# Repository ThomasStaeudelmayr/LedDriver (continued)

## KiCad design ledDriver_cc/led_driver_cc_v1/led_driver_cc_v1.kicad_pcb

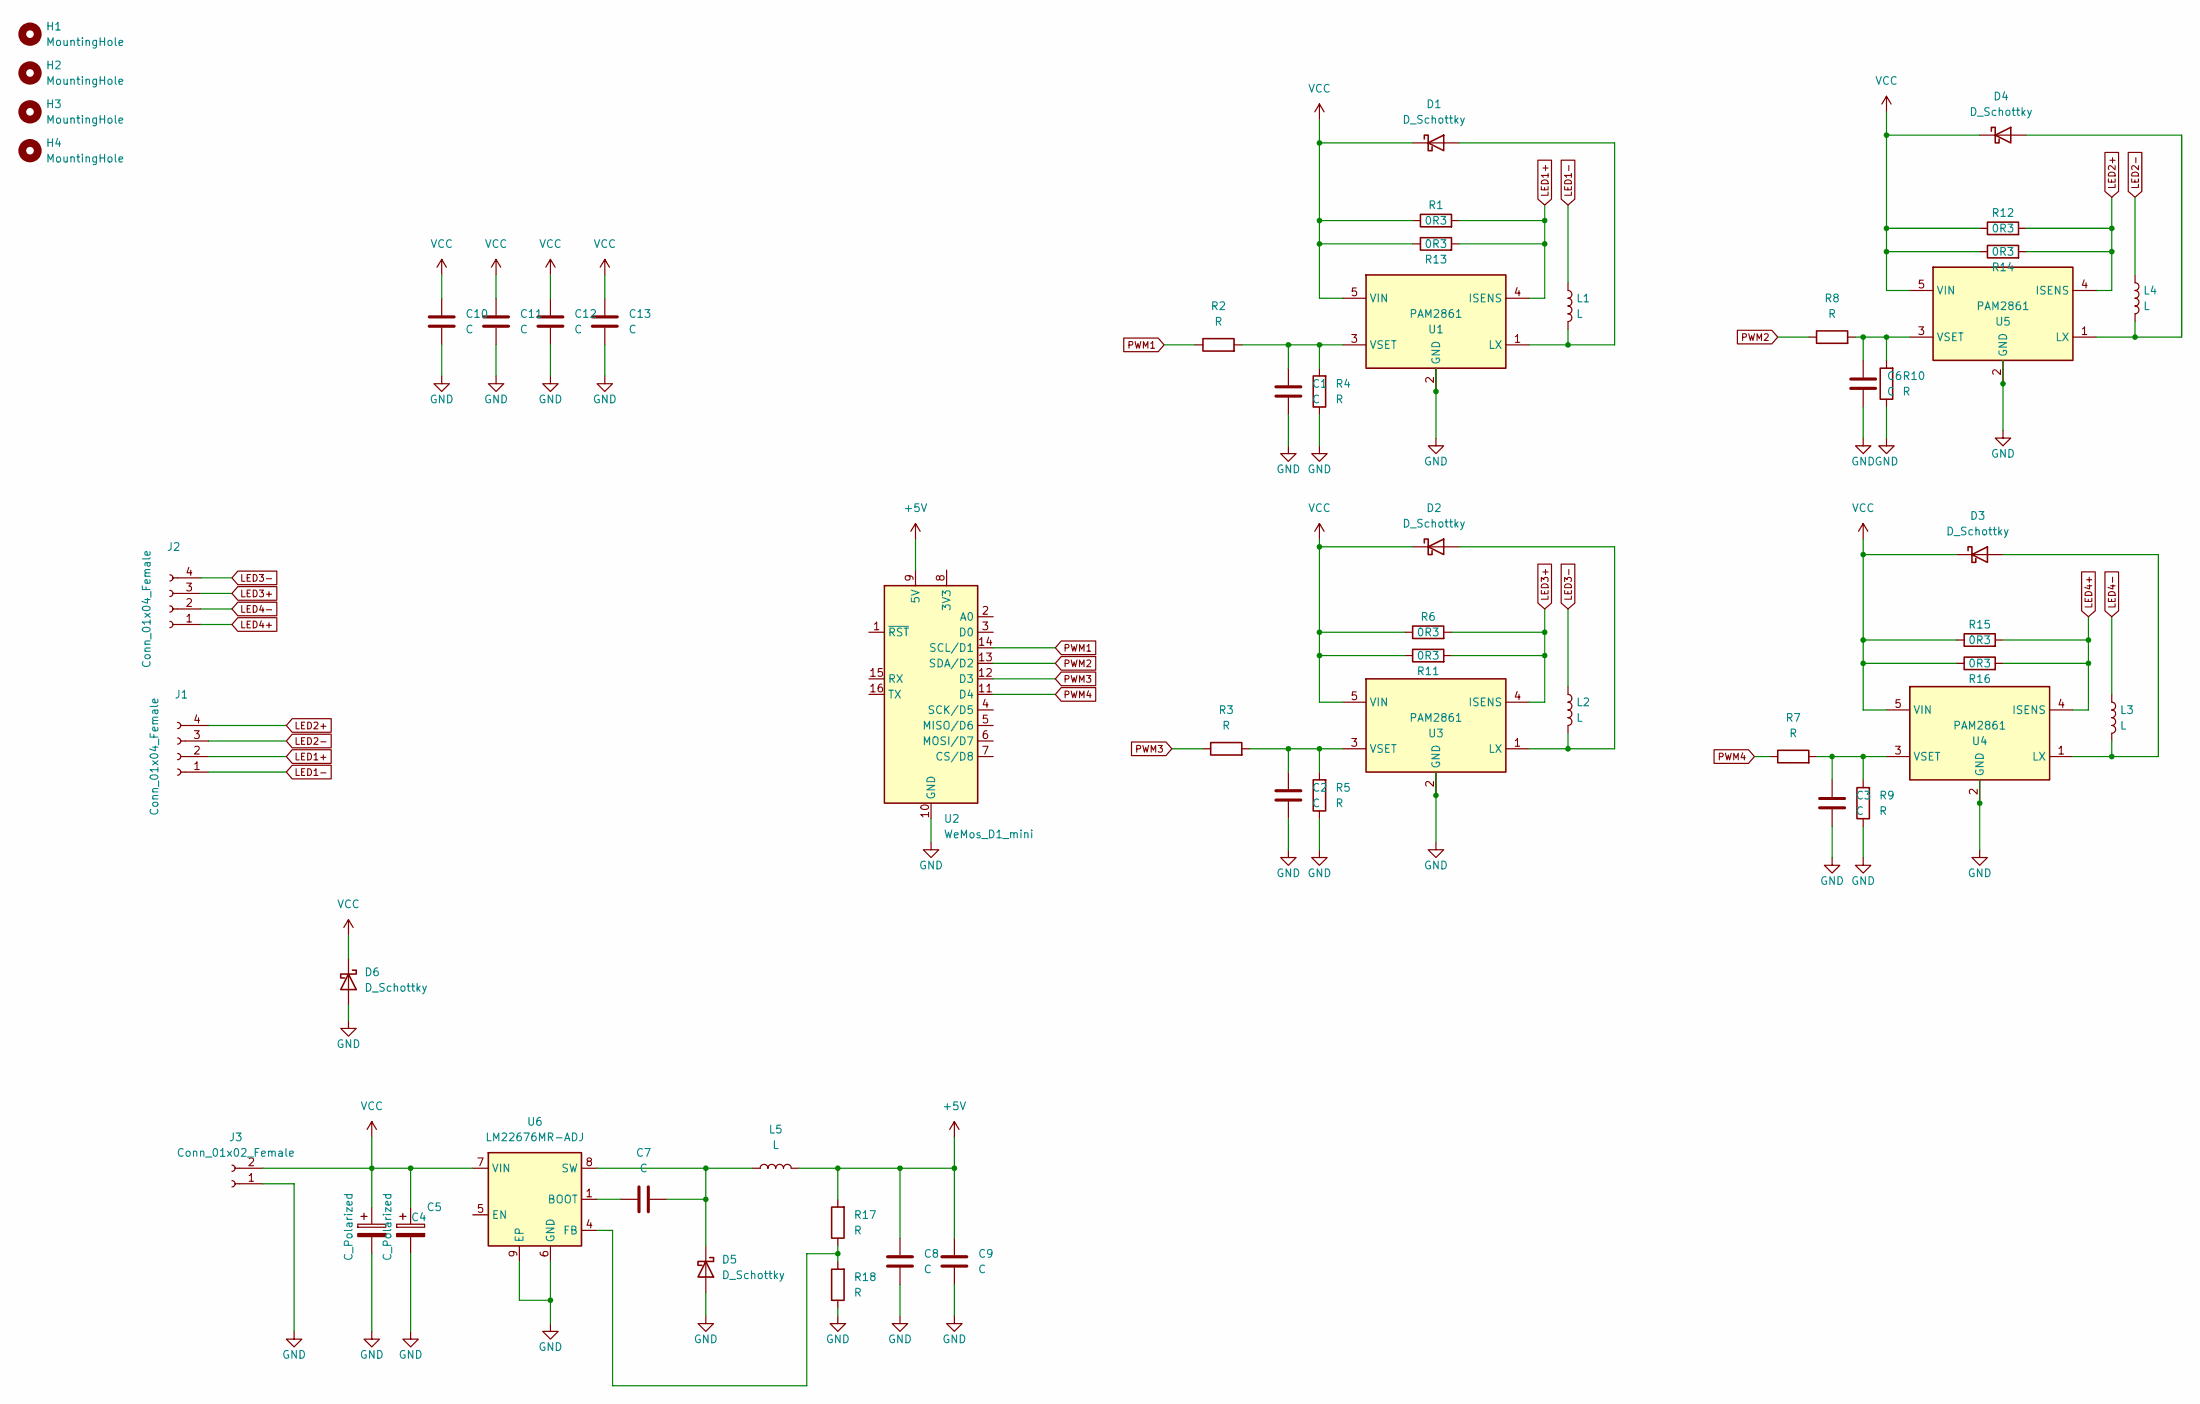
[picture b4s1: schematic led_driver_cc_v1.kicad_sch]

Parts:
C1, C2, C3, C6, C7: C; C_1206_3216Metric_Pad1.33x1.80mm_HandSolder
C4, C5: C_Polarized; CP_Radial_D13.0mm_P5.00mm
C8, C9, C10, C11, C12, C13: C; C_1210_3225Metric_Pad1.33x2.70mm_HandSolder
D1, D2, D3, D4, D5: D_Schottky; D_SMB
D6: D_Schottky; D_SMC
H1, H2, H3, H4: MountingHole; MountingHole_2.7mm_M2.5_DIN965_Pad_TopBottom
J1, J2: Conn_01x04_Female; PhoenixContact_MSTBVA_2,5_4-G_1x04_P5.00mm_Vertical
J3: Conn_01x02_Female; PhoenixContact_MSTBVA_2,5_2-G_1x02_P5.00mm_Vertical
L1, L2, L3, L4, L5: L; L_10.4x10.4_H4.8
R1, R6, R11, R12, R13, R14, R15, R16: 0R3; R_1206_3216Metric
R2, R3, R4, R5, R7, R8, R9, R10, R17, R18: R; R_1206_3216Metric
U1, U3, U4, U5: PAM2861; SOT-89
U2: WeMos_D1_mini; WEMOS_D1_mini_light
U6: LM22676MR-ADJ; TI_SO-PowerPAD-8

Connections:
+5V: C8.1, C9.1, L5.2, R17.2, U2.9 (5V)
GND: C1.2, C2.2, C3.2, C4.2, C5.2, C6.2, C8.2, C9.2, C10.2, C11.2, C12.2, C13.2, D5.2 (A), D6.2 (A), J3.1, R4.1, R5.1, R9.1, R10.1, R18.1, U1.2 (GND), U2.10 (GND), U3.2 (GND), U4.2 (GND), U5.2 (GND), U6.6 (GND), U6.9 (EP)
LED1+: J1.2, R1.2, R13.2, U1.4 (ISENS)
LED1-: J1.1, L1.1
LED2+: J1.4, R12.2, R14.2, U5.4 (ISENS)
LED2-: J1.3, L4.1
LED3+: J2.3, R6.2, R11.2, U3.4 (ISENS)
LED3-: J2.4, L2.1
LED4+: J2.1, R15.2, R16.2, U4.4 (ISENS)
LED4-: J2.2, L3.1
unnamed: C1.1, R2.2, R4.2, U1.3 (VSET)
unnamed: C2.1, R3.2, R5.2, U3.3 (VSET)
unnamed: C3.1, R7.2, R9.2, U4.3 (VSET)
unnamed: C6.1, R8.2, R10.2, U5.3 (VSET)
unnamed: C7.1, U6.1 (BOOT)
unnamed: C7.2, D5.1 (K), L5.1, U6.8 (SW)
unnamed: D1.2 (A), L1.2, U1.1 (LX)
unnamed: D2.2 (A), L2.2, U3.1 (LX)
unnamed: D3.2 (A), L3.2, U4.1 (LX)
unnamed: D4.2 (A), L4.2, U5.1 (LX)
unnamed: R17.1, R18.2, U6.4 (FB)
PWM1: R2.1, U2.14 (SCL/D1)
PWM2: R8.1, U2.13 (SDA/D2)
PWM3: R3.1, U2.12 (D3)
PWM4: R7.1, U2.11 (D4)
VCC: C4.1, C5.1, C10.1, C11.1, C12.1, C13.1, D1.1 (K), D2.1 (K), D3.1 (K), D4.1 (K), D6.1 (K), J3.2, R1.1, R6.1, R11.1, R12.1, R13.1, R14.1, R15.1, R16.1, U1.5 (VIN), U3.5 (VIN), U4.5 (VIN), U5.5 (VIN), U6.7 (VIN)

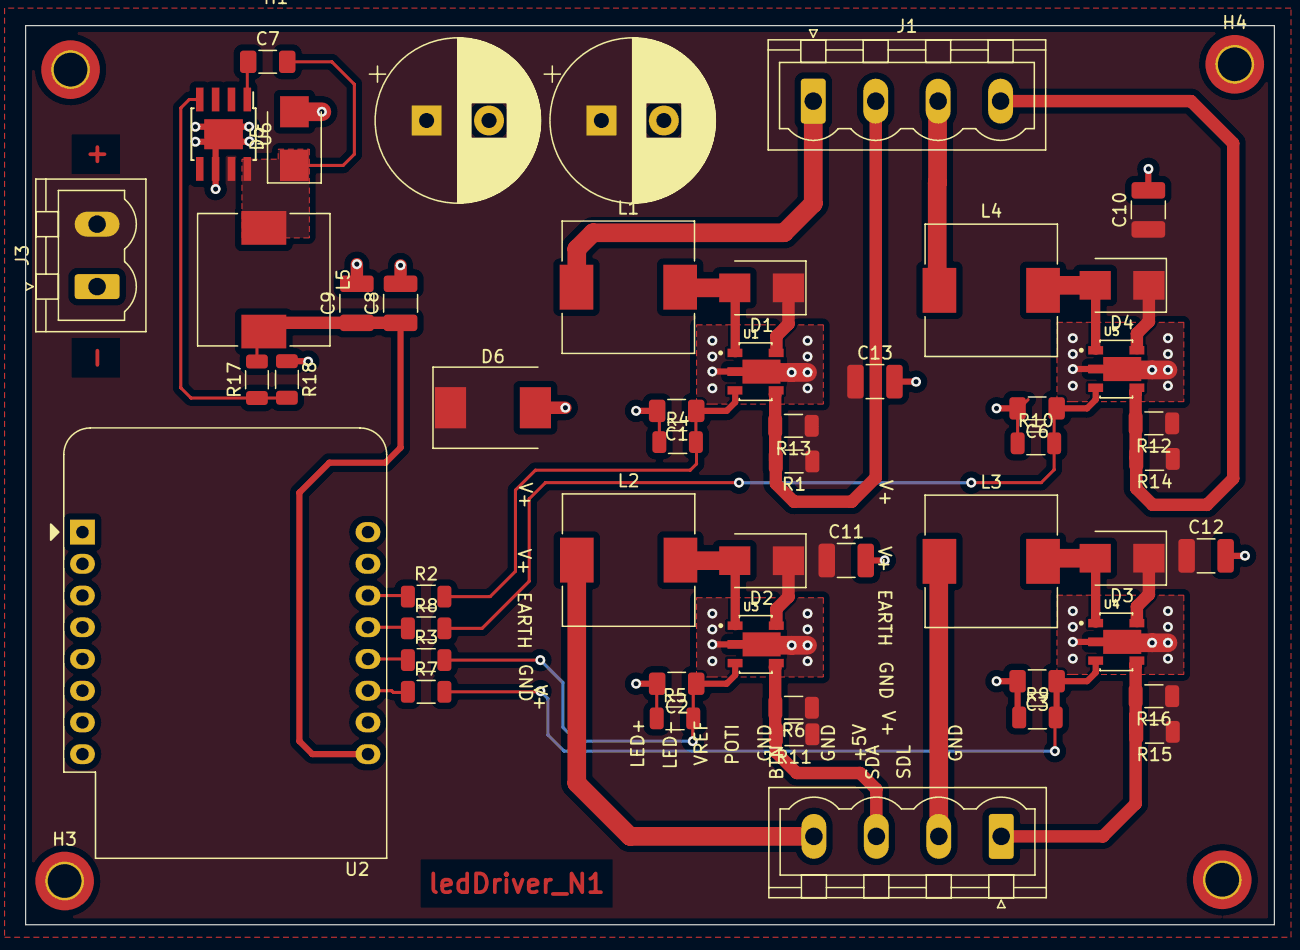
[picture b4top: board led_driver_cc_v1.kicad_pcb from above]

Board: 2 copper layers, 100.0 x 72.0 mm, 55 parts (0 on the bottom side), 26 nets.

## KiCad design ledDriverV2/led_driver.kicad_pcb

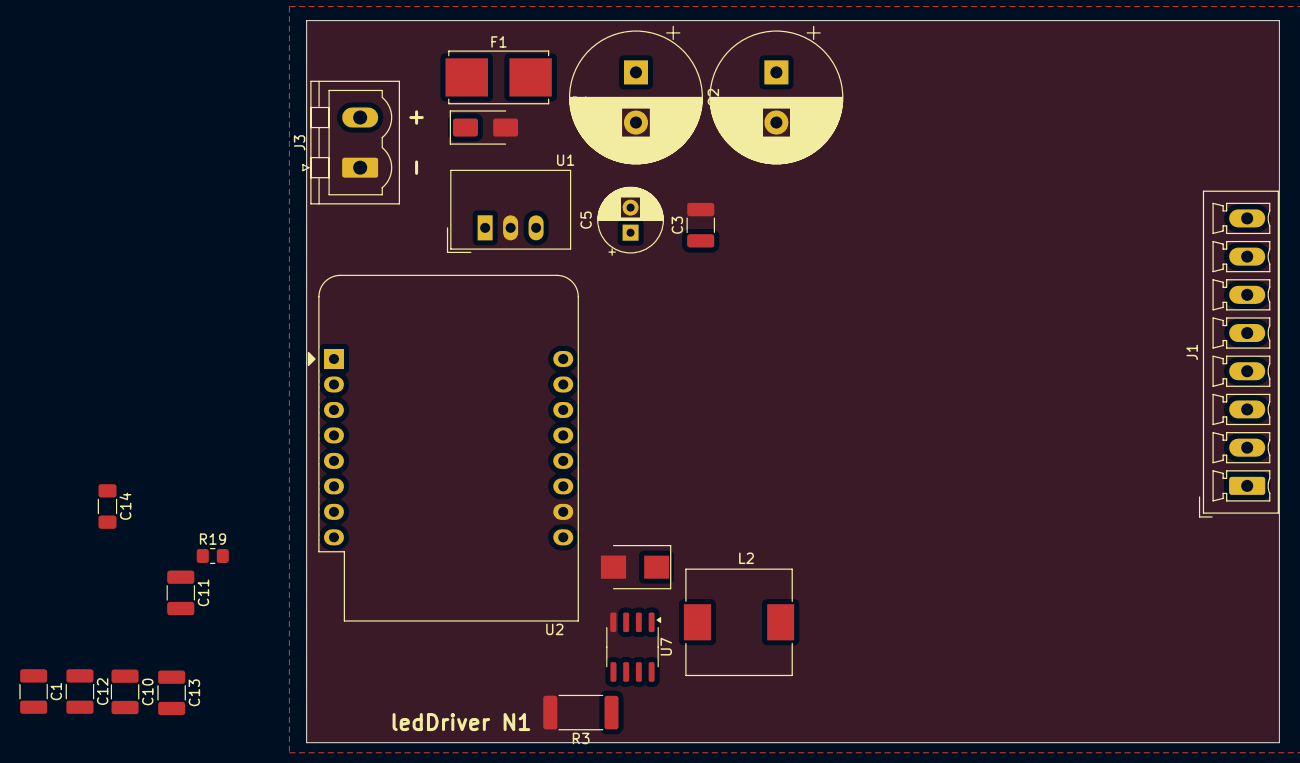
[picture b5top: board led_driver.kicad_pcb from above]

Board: 2 copper layers, 97.0 x 72.0 mm, 21 parts (0 on the bottom side), 11 nets, no tracks yet.

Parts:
C1, C3, C10, C11, C12, C13: C; C_1210_3225Metric_Pad1.33x2.70mm_HandSolder
C2, C4: C_Polarized; CP_Radial_D13.0mm_P5.00mm
C5: C_Polarized; CP_Radial_D6.3mm_P2.50mm
C14: C; C_1206_3216Metric_Pad1.33x1.80mm_HandSolder
D1: SMAJ40A; D_SMA
D2: D_Schottky; D_SMB
F1: Fuse; Fuseholder_Littelfuse_Nano2_154x
J1: Conn_01x08_Pin; PhoenixContact_MCV_1,5_8-G-3.81_1x08_P3.81mm_Vertical
J3: Conn_01x02_Female; PhoenixContact_MSTBVA_2,5_2-G_1x02_P5.00mm_Vertical
L2: L; L_10.4x10.4_H4.8
R3: R; R_2512_6332Metric_Pad1.40x3.35mm_HandSolder
R19: R; R_0805_2012Metric_Pad1.20x1.40mm_HandSolder
U1: TSR_1-2490; Converter_DCDC_TRACO_TSR-1_THT
U2: WeMos_D1_mini; WEMOS_D1_mini_light
U7: SOIC-8_3.9x4.9mm_P1.27mm

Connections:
GND: C1.2, C2.2, C3.2, C4.2, C5.2, C10.2, C11.2, C12.2, C13.2, D1.2 (A2), D2.2 (A), J3.1, R3.2, U1.2 (GND), U2.10 (GND), U7.4 (GND)
LED3+: J1.2, L2.2
LED3-: J1.1, R3.1, U7.5 (CS)
unnamed: D1.1 (A1), F1.1, J3.2
unnamed: C14.2, D2.1 (K), L2.1, U7.1 (SW)
unnamed: C2.1, C4.1, F1.2, U1.1 (Vin)
unnamed: C14.1, U7.2 (BOOT)
unnamed: R19.1, U7.6 (RON)
unnamed: C1.1, U7.7 (VCC)
PWM3: U2.12 (D3), U7.3 (DIM)
VCC: C3.1, C5.1, C10.1, C11.1, C12.1, C13.1, R19.2, U1.3 (Vout), U7.8 (VIN)

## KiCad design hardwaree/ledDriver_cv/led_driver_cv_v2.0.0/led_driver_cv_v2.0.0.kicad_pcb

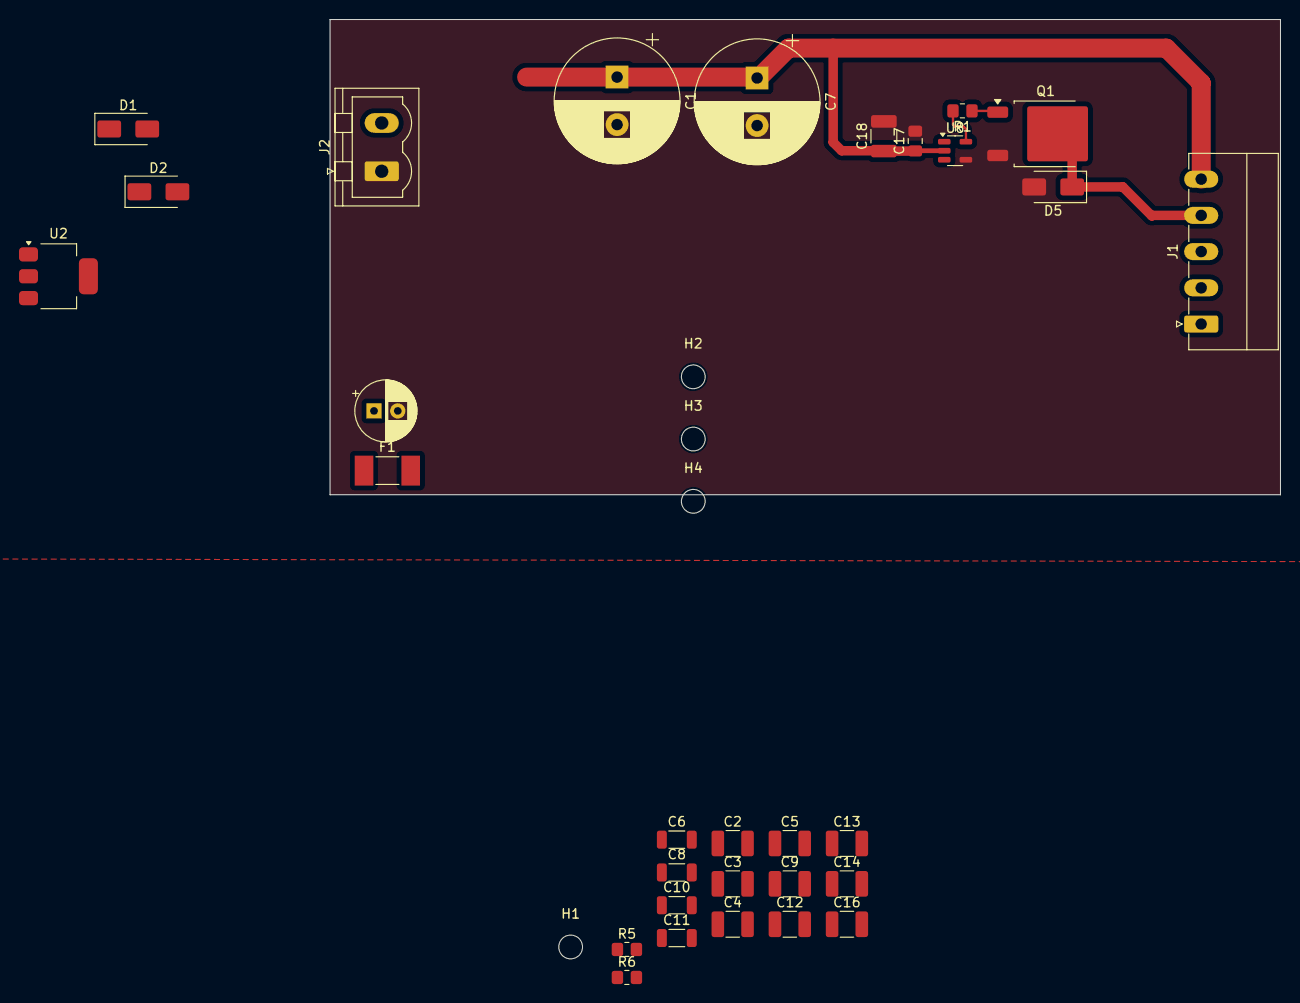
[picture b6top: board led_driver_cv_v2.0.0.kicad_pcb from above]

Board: 2 copper layers, 100.0 x 50.0 mm, 34 parts (0 on the bottom side), 10 nets.

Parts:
C1, C7: C_Polarized; CP_Radial_D13.0mm_P5.00mm
C2, C3, C4, C5, C9, C12, C13, C14, C16: C; C_1210_3225Metric_Pad1.33x2.70mm_HandSolder
C6, C8, C10, C11: C; L_1206_3216Metric
C15: C_Polarized; CP_Radial_D6.3mm_P2.50mm
C17: 100n; C_0805_2012Metric_Pad1.18x1.45mm_HandSolder
C18: 10uF; C_1210_3225Metric_Pad1.33x2.70mm_HandSolder
D1, D5: SMAJ40A; D_SMA
D2: US1M; D_SMA
F1: Fuse; Fuse_Littelfuse-NANO2-451_453
H1, H2, H3, H4: MountingHole; MountingHole_2.5mm
J1: Conn_01x05_Socket; PhoenixContact_MC_1,5_5-G-3.81_1x05_P3.81mm_Horizontal
J2: Conn_01x02_Female; PhoenixContact_MSTBVA_2,5_2-G-5,08_1x02_P5.08mm_Vertical
Q1: QM6006D; TO-252-2
R1: 10R; R_0805_2012Metric_Pad1.20x1.40mm_HandSolder
R5, R6: R; R_0805_2012Metric_Pad1.20x1.40mm_HandSolder
U2: LM317_SOT-223; SOT-223-3_TabPin2
U8: MCP1416; SOT-23-5

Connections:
9V: R6.1, U2.2 (VO)
+5V: C15.1, C16.1, D2.2 (A)
+10V: C6.1, C8.1, C10.1, C11.1
CH1: D5.1 (A1), J1.4, Q1.2 (D)
GND: C1.2, C2.2, C3.2, C4.2, C5.2, C6.2, C7.2, C8.2, C9.2, C10.2, C11.2, C12.2, C13.2, C14.2, C15.2, C16.2, C17.2, C18.2, D1.2 (A2), D5.2 (A2), J2.1, Q1.3 (S), R5.2, U8.4 (GND)
unnamed: D1.1 (A1), F1.1, J2.2
unnamed: Q1.1 (G), R1.1
unnamed: R5.1, R6.2, U2.1 (ADJ)
unnamed: R1.2, U8.5 (OUT)
VCC: C1.1, C2.1, C3.1, C4.1, C5.1, C7.1, C9.1, C12.1, C13.1, C14.1, C17.1, C18.1, F1.2, J1.5, U2.3 (VI), U8.2 (Vdd)

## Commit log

2025-06-21 added files
2025-06-21 add files
2025-06-22 file renaming
2025-06-24 add partslib
2025-06-26 more custom parts
2025-06-26 step files in folders
2025-06-28 removed lib
2025-08-16 add new channels to led driver
2025-08-17 new channel arrangement
2026-02-07 add code
2026-03-19 add media and new foler structure
2026-03-20 ESP32 receiver and transmitter
2026-03-20 add web apps
2026-05-13 bug fix
2026-05-13 add read me
2026-05-23 removed images
2026-05-23 add img
2026-05-24 new python files
2026-05-24 remove env folder
2026-05-24 webserver example
2026-05-24 rework README
2026-05-24 downscale img
2026-05-24 removed backups
2026-05-24 Add 5A fuse to components list in README
